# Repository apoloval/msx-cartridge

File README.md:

# MSX Cartridge

Some hardware specs (schematics + PCB designs) to build cartridges for MSX system.

This PCB can be used to mimic old cartridges for the MSX system. 
It will fit any ROM dump <64kb. Dumps larger than 64kb need a mapper, not implemented in this version.

EPROM supported is the SST39 family that can be bought for around 1.5€. This EPROM can be programmed with a standard TL866 programmer.

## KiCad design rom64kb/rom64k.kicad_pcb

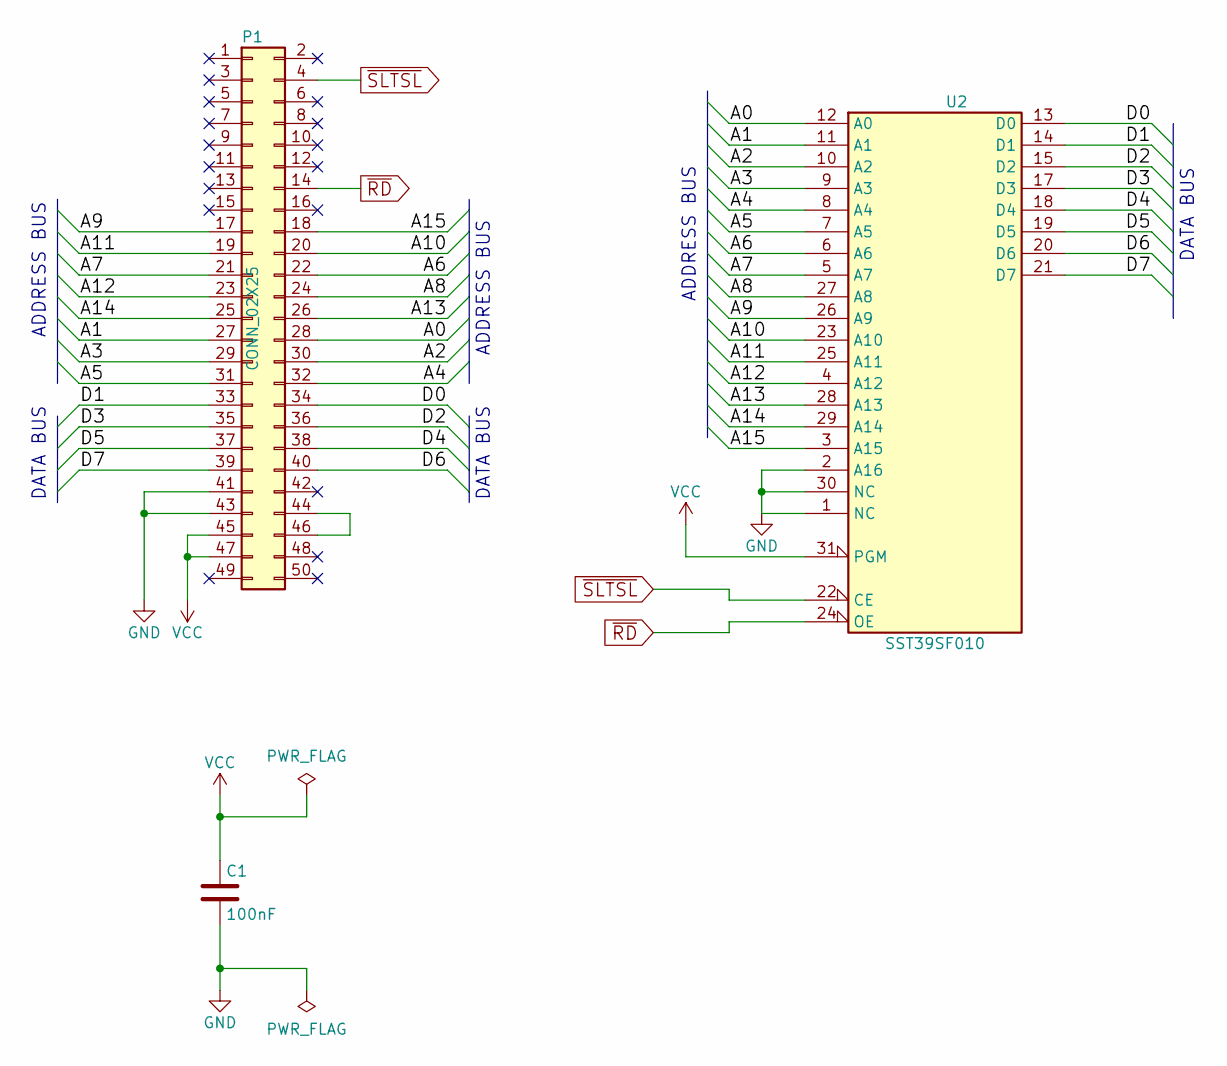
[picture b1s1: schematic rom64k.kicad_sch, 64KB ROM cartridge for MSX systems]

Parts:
C1: 100nF; C_Disc_D6_P5
P1: CONN_02X25; msx_cartridge
U2: SST39SF010; DIP-32_W15.24mm

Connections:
/A0: P1.28, U2.12 (A0)
/A1: P1.27, U2.11 (A1)
/A2: P1.30, U2.10 (A2)
/A3: P1.29, U2.9 (A3)
/A4: P1.32, U2.8 (A4)
/A5: P1.31, U2.7 (A5)
/A6: P1.22, U2.6 (A6)
/A7: P1.21, U2.5 (A7)
/A8: P1.24, U2.27 (A8)
/A9: P1.17, U2.26 (A9)
/A10: P1.20, U2.23 (A10)
/A11: P1.19, U2.25 (A11)
/A12: P1.23, U2.4 (A12)
/A13: P1.26, U2.28 (A13)
/A14: P1.25, U2.29 (A14)
/A15: P1.18, U2.3 (A15)
/D0: P1.34, U2.13 (D0)
/D1: P1.33, U2.14 (D1)
/D2: P1.36, U2.15 (D2)
/D3: P1.35, U2.17 (D3)
/D4: P1.38, U2.18 (D4)
/D5: P1.37, U2.19 (D5)
/D6: P1.40, U2.20 (D6)
/D7: P1.39, U2.21 (D7)
GND: C1.2, P1.41, P1.43, U2.1 (NC), U2.2 (A16), U2.16 (GND), U2.30 (NC)
unnamed: P1.44, P1.46
VCC: C1.1, P1.45, P1.47, U2.31 (PGM), U2.32 (VCC)
~RD: P1.14, U2.24 (OE)
~SLTSL: P1.4, U2.22 (CE)

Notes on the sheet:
DATA BUS
ADDRESS BUS

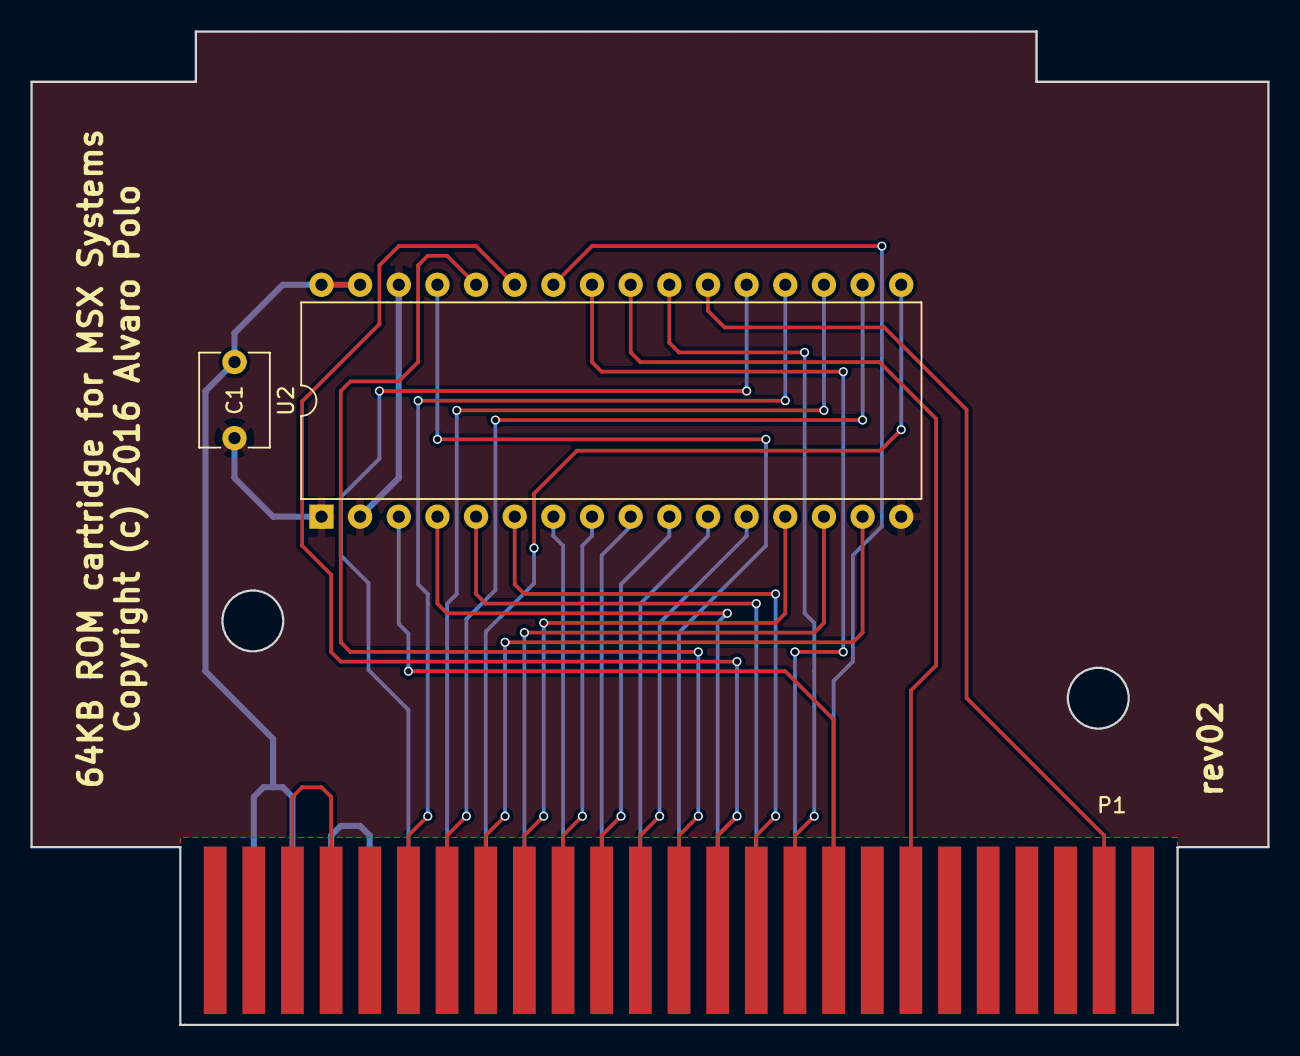
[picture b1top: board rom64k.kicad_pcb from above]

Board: 2 copper layers, 81.3 x 65.3 mm, 3 parts (0 on the bottom side), 29 nets.

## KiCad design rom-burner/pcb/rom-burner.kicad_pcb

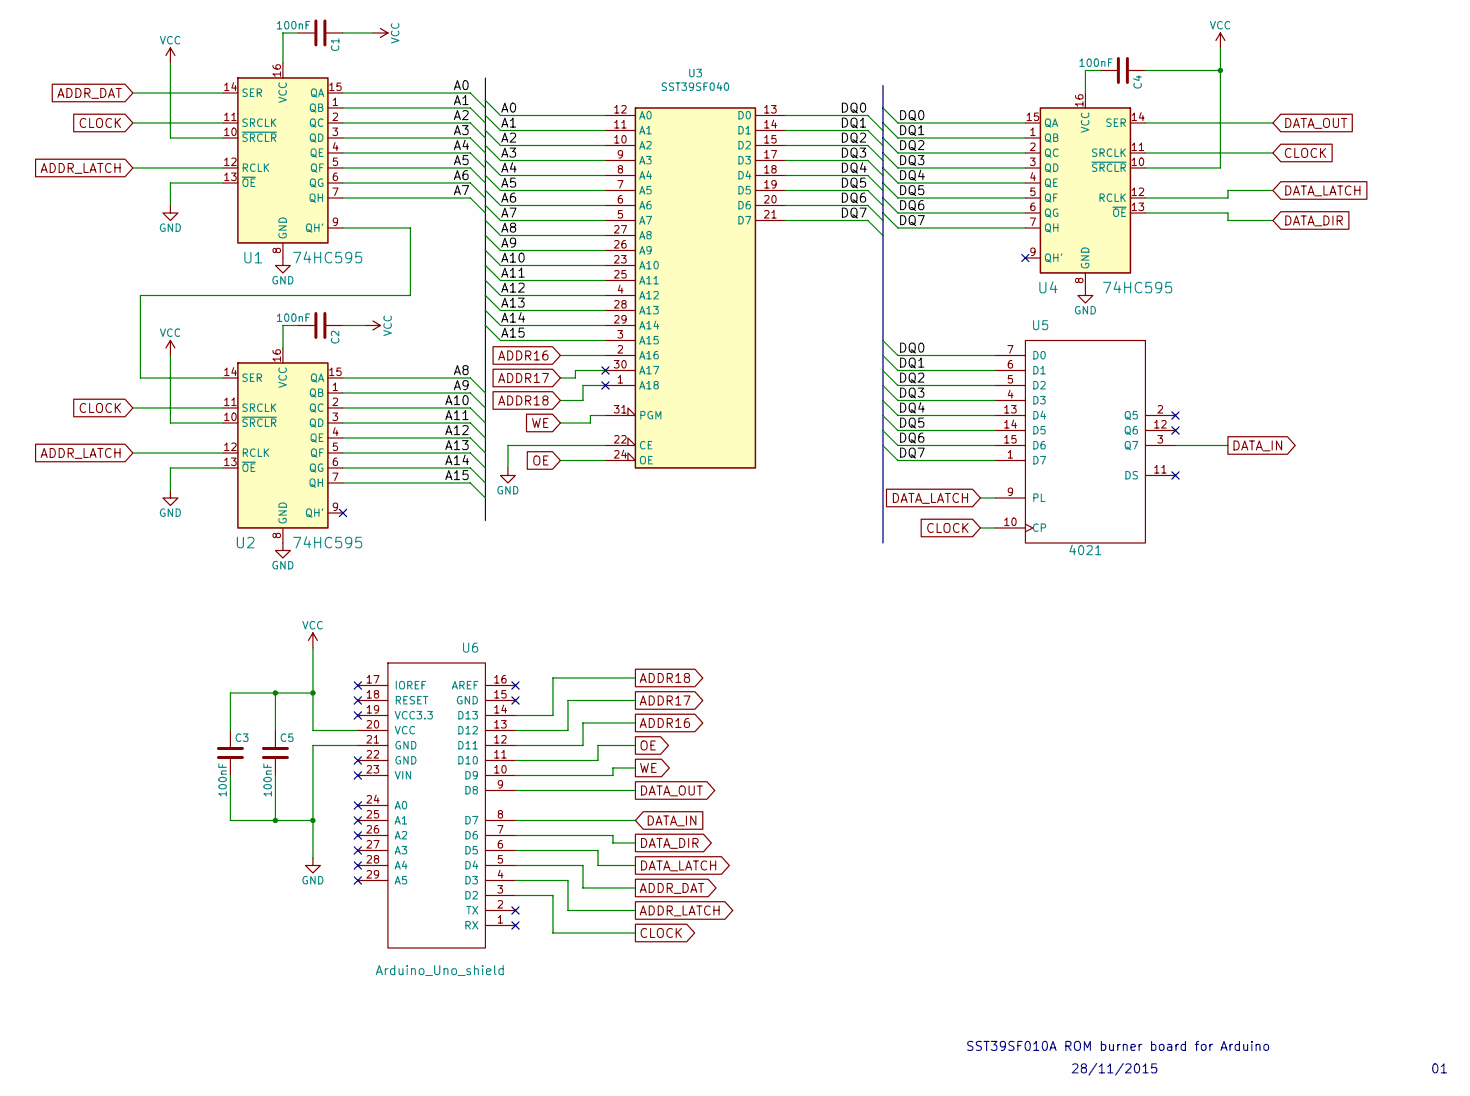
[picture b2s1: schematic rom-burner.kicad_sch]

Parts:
C1, C2, C3, C4, C5: 100nF; C_Rect_L7.0mm_W2.5mm_P5.00mm
U1, U2, U4: 74HC595; DIP-16_W7.62mm
U3: SST39SF040; DIP-32_W15.24mm_LongPads
U5: 4021; DIP-16_W7.62mm
U6: Arduino_Uno_shield; arduino_uno_shield

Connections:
/A0: U1.15 (QA), U3.12 (A0)
/A1: U1.1 (QB), U3.11 (A1)
/A2: U1.2 (QC), U3.10 (A2)
/A3: U1.3 (QD), U3.9 (A3)
/A4: U1.4 (QE), U3.8 (A4)
/A5: U1.5 (QF), U3.7 (A5)
/A6: U1.6 (QG), U3.6 (A6)
/A7: U1.7 (QH), U3.5 (A7)
/A8: U2.15 (QA), U3.27 (A8)
/A9: U2.1 (QB), U3.26 (A9)
/A10: U2.2 (QC), U3.23 (A10)
/A11: U2.3 (QD), U3.25 (A11)
/A12: U2.4 (QE), U3.4 (A12)
/A13: U2.5 (QF), U3.28 (A13)
/A14: U2.6 (QG), U3.29 (A14)
/A15: U2.7 (QH), U3.3 (A15)
/DQ0: U3.13 (D0), U4.15 (QA), U5.7 (D0)
/DQ1: U3.14 (D1), U4.1 (QB), U5.6 (D1)
/DQ2: U3.15 (D2), U4.2 (QC), U5.5 (D2)
/DQ3: U3.17 (D3), U4.3 (QD), U5.4 (D3)
/DQ4: U3.18 (D4), U4.4 (QE), U5.13 (D4)
/DQ5: U3.19 (D5), U4.5 (QF), U5.14 (D5)
/DQ6: U3.20 (D6), U4.6 (QG), U5.15 (D6)
/DQ7: U3.21 (D7), U4.7 (QH), U5.1 (D7)
ADDR16: U3.2 (A16), U6.12 (D11)
ADDR17: U3.30 (A17), U6.13 (D12)
ADDR18: U3.1 (A18), U6.14 (D13)
ADDR_DAT: U1.14 (SER), U6.5 (D4)
ADDR_LATCH: U1.12 (RCLK), U2.12 (RCLK), U6.4 (D3)
CLOCK: U1.11 (SRCLK), U2.11 (SRCLK), U4.11 (SRCLK), U5.10 (CP), U6.3 (D2)
DATA_DIR: U4.13 (~OE), U6.7 (D6)
DATA_IN: U5.3 (Q7), U6.8 (D7)
DATA_LATCH: U4.12 (RCLK), U5.9 (PL), U6.6 (D5)
DATA_OUT: U4.14 (SER), U6.9 (D8)
GND: C3.2, C5.2, U1.8 (GND), U1.13 (~OE), U2.8 (GND), U2.13 (~OE), U3.16 (GND), U3.22 (CE), U4.8 (GND), U5.8 (GND), U6.21 (GND)
unnamed: C1.2, U1.16 (VCC)
unnamed: C2.2, U2.16 (VCC)
unnamed: C4.2, U4.16 (VCC)
unnamed: U1.9 (QH'), U2.14 (SER)
OE: U3.24 (OE), U6.11 (D10)
VCC: C1.1, C2.1, C3.1, C4.1, C5.1, U1.10 (~SRCLR), U2.10 (~SRCLR), U3.32 (VCC), U4.10 (~SRCLR), U5.16 (VCC), U6.20 (VCC)
WE: U3.31 (PGM), U6.10 (D9)

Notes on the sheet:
SST39SF010A ROM burner board for Arduino
28/11/2015

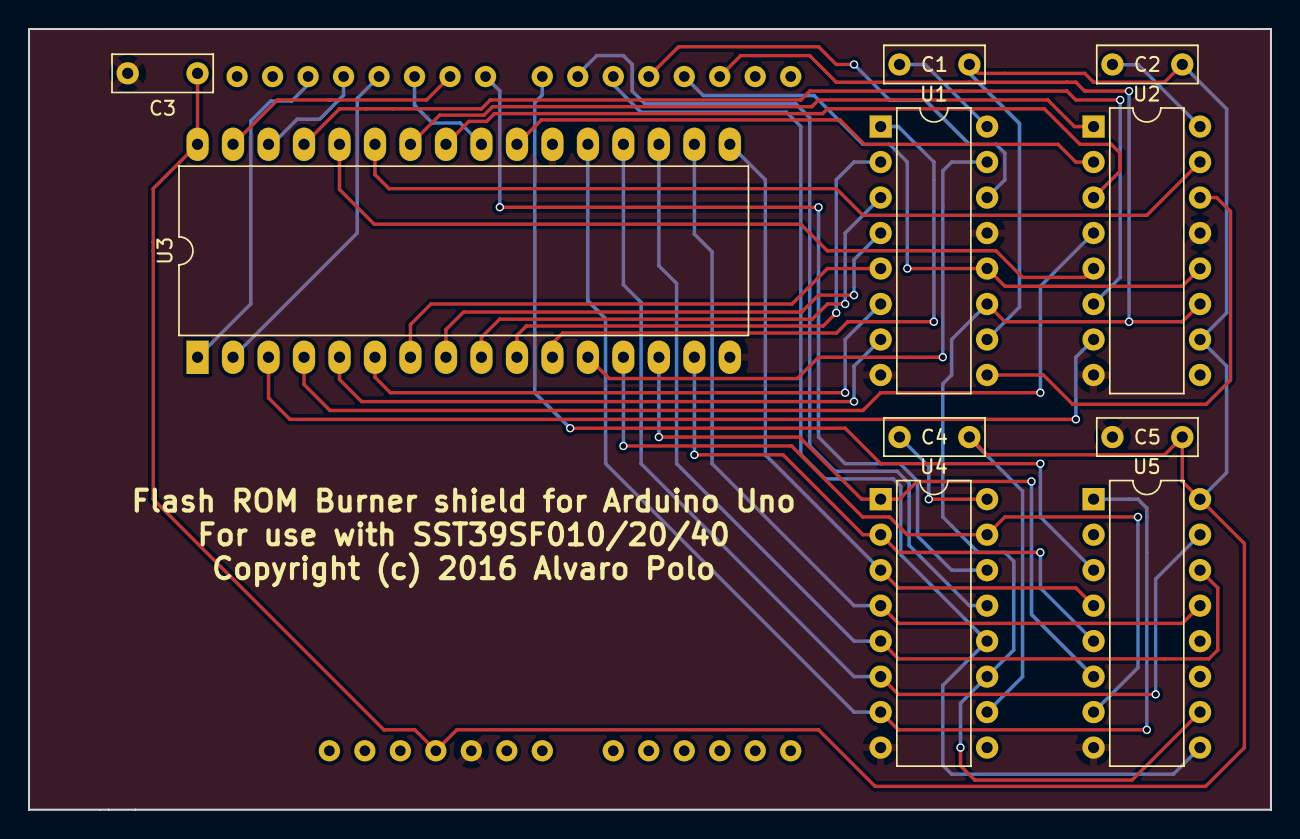
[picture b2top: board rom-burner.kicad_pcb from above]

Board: 2 copper layers, 88.9 x 55.9 mm, 11 parts (0 on the bottom side), 42 nets.

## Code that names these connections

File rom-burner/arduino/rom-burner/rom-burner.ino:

#define PIN_CLOCK         2
#define PIN_ADDR_LATCH    3
#define PIN_ADDR_OUT      4
#define PIN_DATA_LATCH    5
#define PIN_DATA_READ     6
#define PIN_DATA_IN       7
#define PIN_DATA_OUT      8
#define PIN_WE            9
#define PIN_OE            10
#define PIN_ADDR16        11
#define PIN_ADDR17        12
#define PIN_ADDR18        13

#define SECTOR_SIZE       4096

#define COMMAND_READ      0
#define COMMAND_ERASE     1
#define COMMAND_WRITE     2
#define COMMAND_ERASEALL  3

#define SERIAL_BAUDRATE 921600

/** Put the given address in the bus through shift out registers. */
void put_addr(unsigned long addr) {
  digitalWrite(PIN_ADDR_LATCH, LOW);
  digitalWrite(PIN_CLOCK, LOW);
  shiftOut(PIN_ADDR_OUT, PIN_CLOCK, MSBFIRST, (byte) (addr >> 8));
  shiftOut(PIN_ADDR_OUT, PIN_CLOCK, MSBFIRST, (byte) addr);
  digitalWrite(PIN_ADDR16, bitRead(addr, 16));
  digitalWrite(PIN_ADDR17, bitRead(addr, 17));
  digitalWrite(PIN_ADDR18, bitRead(addr, 18));
  digitalWrite(PIN_ADDR_LATCH, HIGH);
}

/** Put the given data in the bus through shift out registers. */
void put_data(byte data) {
  digitalWrite(PIN_DATA_LATCH, LOW);
  digitalWrite(PIN_CLOCK, LOW);
  shiftOut(PIN_DATA_OUT, PIN_CLOCK, MSBFIRST, (byte) data);
  digitalWrite(PIN_DATA_LATCH, HIGH);
}

/** Get data from the data bus. */
byte get_data() {
  digitalWrite(PIN_OE, LOW);
  digitalWrite(PIN_CLOCK, HIGH);
  digitalWrite(PIN_DATA_LATCH, HIGH);
  digitalWrite(PIN_DATA_LATCH, LOW);
  digitalWrite(PIN_OE, HIGH);
  return shiftIn(PIN_DATA_IN, PIN_CLOCK, MSBFIRST);
}

/** Send a command to the ROM device. */
void send_cmd_seq(unsigned long* addr, byte* data, unsigned len) {
  digitalWrite(PIN_DATA_READ, LOW);
  digitalWrite(PIN_OE, HIGH);
  for (int i = 0; i < len; i++) {
    put_addr(addr[i]);
    digitalWrite(PIN_WE, LOW);
    put_data(data[i]);
    digitalWrite(PIN_WE, HIGH);
  }
  digitalWrite(PIN_DATA_READ, HIGH);
}

/** Read the content of given ROM device address. */
byte read_addr(unsigned long addr) {
  put_addr(addr);
  return get_data();
}

/** Wait for write/erase operation using data polling method. */
void wait_datapolling(byte data) {
  for (;;) {
    byte recv = get_data();
    if ((recv & 0x80) == (data & 0x80))
      return;
  }
}

/**
 * Write the content of the given ROM device address
 * with the given byte.
 */
void write_addr(unsigned long addr, byte data) {
  unsigned long addr_seq[] = { 0x5555, 0x2aaa, 0x5555, addr };
  byte data_seq[] = { 0xaa, 0x55, 0xa0, data };
  send_cmd_seq(addr_seq, data_seq, 4);
  wait_datapolling(data);
}

/**
 * Perform a blank test, returning the number of bytes that
 * are not equal to 0xff.
 */
int blank_test(byte sector) {
  unsigned long sector_addr = ((unsigned long) sector) << 12;
  int result = 0;
  for (int i = 0; i < SECTOR_SIZE; i++) {
    unsigned long addr = sector_addr + i;
    byte actual = read_addr(addr);
    if (actual != 0xff) {
      result++;
    }
  }
  return result;
}

/** Erase the whole memory. */
int erase_all() {
  unsigned long addr_seq[] = { 0x5555, 0x2aaa, 0x5555, 0x5555, 0x2aaa, 0x5555 };
  byte data_seq[] = { 0xaa, 0x55, 0x80, 0xaa, 0x55, 0x10 };
  send_cmd_seq(addr_seq, data_seq, 6);
  delay(500);
  return blank_test(0);
}

/** Erase the given sector. */
int erase_sector(byte sector) {
  unsigned long sector_addr = ((unsigned long) sector) << 12;
  unsigned long addr_seq[] = { 0x5555, 0x2aaa, 0x5555, 0x5555, 0x2aaa, sector_addr };
  byte data_seq[] = { 0xaa, 0x55, 0x80, 0xaa, 0x55, 0x30 };
  send_cmd_seq(addr_seq, data_seq, 6);
  delay(20);
  return blank_test(sector);
}

/** Read a single byte from serial, waiting if none has arrived yet. */
byte serial_read_byte() {
  while (Serial.available() < 1) {}
  return Serial.read();
}

/** Process a incoming read command from serial. */
void process_read_command() {
  unsigned long sector_addr = ((unsigned long) serial_read_byte()) << 12;
  for (int i = 0; i < SECTOR_SIZE; i++) {
    unsigned long addr = sector_addr + i;
    byte data = read_addr(addr);
    Serial.write(data);
  }
}

/** Process a incoming erase command from serial. */
void process_erase_command() {
  byte sector = serial_read_byte();
  Serial.write(erase_sector(sector));
}

/** Process a incoming erase command from serial. */
void process_eraseall_command() {
  Serial.write(erase_all());
}

/** Process a incoming write command from serial. */
void process_write_command() {
  unsigned long sector_addr = ((unsigned long) serial_read_byte()) << 12;
  for (int i = 0; i < SECTOR_SIZE; i++) {
    unsigned long addr = sector_addr + i;
    byte data = serial_read_byte();
    write_addr(addr, data);
    Serial.write(data);
  }
}

/** Process a incoming command from serial. */
void process_command() {
  switch (serial_read_byte()) {
    case COMMAND_READ:
      process_read_command();
      break;
    case COMMAND_ERASE:
      process_erase_command();
      break;
    case COMMAND_WRITE:
      process_write_command();
      break;
    case COMMAND_ERASEALL:
      process_eraseall_command();
      break;
  }
}

void setup() {
  pinMode(PIN_CLOCK, OUTPUT);
  pinMode(PIN_ADDR_LATCH, OUTPUT);
  pinMode(PIN_ADDR_OUT, OUTPUT);
  pinMode(PIN_DATA_LATCH, OUTPUT);
  pinMode(PIN_DATA_READ, OUTPUT);
  pinMode(PIN_DATA_IN, INPUT);
  pinMode(PIN_DATA_OUT, OUTPUT);
  pinMode(PIN_WE, OUTPUT);
  pinMode(PIN_OE, OUTPUT);
  pinMode(PIN_ADDR16, OUTPUT);
  pinMode(PIN_ADDR17, OUTPUT);
  pinMode(PIN_ADDR18, OUTPUT);

  digitalWrite(PIN_ADDR_LATCH, LOW);
  digitalWrite(PIN_DATA_LATCH, LOW);
  digitalWrite(PIN_DATA_READ, HIGH);
  digitalWrite(PIN_WE, HIGH);
  digitalWrite(PIN_OE, HIGH);
  delay(100);

  Serial.begin(SERIAL_BAUDRATE);
  Serial.write("ROM-BURNER");
}

void loop() {
  process_command();
}

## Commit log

2015-12-30 Make it so
2015-12-30 Add initial files for ROM128K project
2016-01-18 Complete 128KB ROM cartridge schematics & PCB
2016-01-18 Introduce schematics & PCB for a ROM burner device
2016-08-07 Remove dependency from rescue library in rom-burner
2016-08-07 Import rom burner Arduino sketch from rom-burner repo
2016-08-07 Adapt rom-burner Arduino sketch to use 18 bit addresses
2016-08-07 Move rom-burner pcb files to its own directory
2016-08-07 Migrate rom-burner cli from legacy repository
2016-08-07 Adapt rom burner cli to support 20 and 40 SST rom models
2016-08-07 Increase baud rate used in rom burner
2016-08-07 Pass serial port by argument in rom burner cli
2016-08-09 Remove net files
    They can (and must) be regenerated from the schematics.
2016-08-09 Add Kicad project for a ROM cartridge of 64KB
2016-08-09 Fix missing tracks in ROM 64KB
2016-08-30 Use a baud rate in burner compatible with Mac OS X
2016-08-30 Fix inlined port name in burner CLI
2016-08-30 Fix broken links to libraries in ROM burner sketch
2019-08-17 Adjust wait time for write ops
2019-08-17 Introduce a new command: eraseall
2019-08-17 Fix obsolete schematic for ROM burner
2019-08-17 [rom-burner] Wait for writes using data polling
2022-01-27 [rom64] Adapt the design to KiCAD 6
2022-01-27 [rom-konami] Add schematic files
2022-03-25 cartridge-breakout: new project

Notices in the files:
rom-burner/pcb/rom-burner.kicad_pcb:
Copyright (c) 2016 Alvaro Polo
